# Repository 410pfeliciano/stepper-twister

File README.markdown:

=================================
An open-source, very fast tetrode twister for Arduino
=================================

This code requires the [Arduino](http://www.arduino.cc) development environment and an [Arduino board](http://www.sparkfun.com/products/11021>). 

The code has been updated to be compatible with the Arduino IDE version 1.0 and higher. To make it compatible with earlier versions of the IDE, simply include "WProgram.h" instead of "Arduino.h" in the TwisterClasses.h file.

This repository contains circuit board files, a parts list, and an instruction manual.

=================================
Attribution
=================================
This work is basically a direct combination of two existing open-source projects:

1. "Tetrode Twister" by Josh Siegle, which is licensed under [GPLv3](http://www.gnu.org/licenses/gpl-3.0.txt)
    * [Josh on Github](https://github.com/jsiegle)
    * [Twister Project](https://github.com/open-ephys/twister)

2. "Easy Driver" by Brian Schmalz, which is  is licensed under [CC-BY-3.0](https://creativecommons.org/licenses/by/3.0/us/)
    * [Brian's site](http://www.schmalzhaus.com/)
    * [Easy Driver Project](http://www.schmalzhaus.com/EasyDriver/)

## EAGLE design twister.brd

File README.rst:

=================================
An open-source, very fast tetrode twister for Arduino
=================================

This code requires the [Arduino](http://www.arduino.cc) development environment and an [Arduino board](http://www.sparkfun.com/products/11021>). 

The code has been updated to be compatible with the Arduino IDE version 1.0 and higher. To make it compatible with earlier versions of the IDE, simply include "WProgram.h" instead of "Arduino.h" in the TwisterClasses.h file.

This repository contains circuit board files, a parts list, and an instruction manual.

=================================
Attribution
=================================
This work is basically a direct combination of two existing open-source projects:

1. "Tetrode Twister" by Josh Siegle, which is licensed under [GPLv3](http://www.gnu.org/licenses/gpl-3.0.txt)
--* [Josh on Github](https://github.com/jsiegle)
--* [Twister Project](https://github.com/open-ephys/twister)

2. "Easy Driver" by Brian Schmalz, which is  is licensed under [CC-BY-3.0](https://creativecommons.org/licenses/by/3.0/us/)
--* [Brian's site](http://www.schmalzhaus.com/)
--* [Easy Driver Project](http://www.schmalzhaus.com/EasyDriver/)

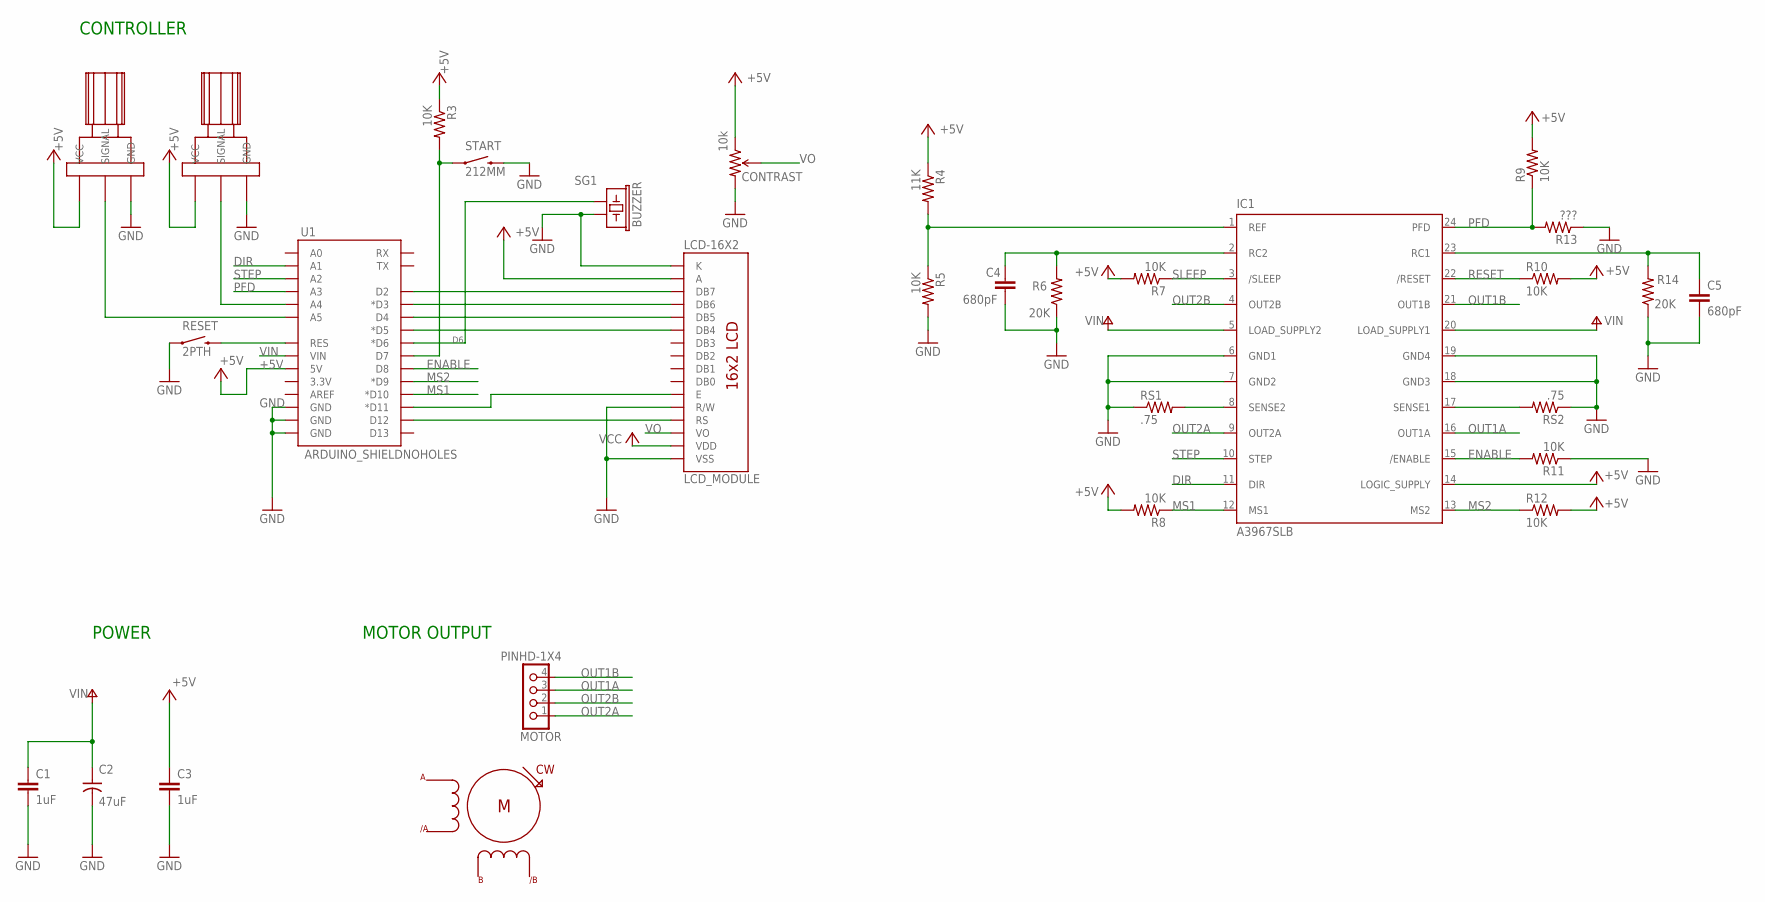
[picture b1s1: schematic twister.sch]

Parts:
BUZZER: SG1; BUZZER-12MM
C1, C3: 1uF; 0805
C2: 47uF; 153CLV-0807
C4, C5: 680pF; 0603
CONTRAST: 10k; 3362U-2
IC1: A3967SLB; SO24W
LCD_MODULE: LCD-16X2
MOTOR: PINHD-1X4; 1X04
R1, R2: R12-0; LARGE_POT
R3, R5, R7, R8, R9, R10, R11, R12: 10K; 0603
R4: 11K; 0603
R6, R14: 20K; 0603
R13: ???; 0603
RESET: 2PTH; TACTILE-PTH
RS1, RS2: .75; 1206
START: 212MM; TACTILE-PTH-12MM
STEPPER: ST-PM35; ST-PM35-15-11C
U1: ARDUINO_SHIELDNOHOLES; DUEMILANOVE_SHIELD_NOHOLES

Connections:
D6: BUZZER.- (2), U1.D6 (*D6)
DIR: IC1.11 (DIR), U1.A1
ENABLE: IC1.15 (/ENABLE), R11.2, U1.D8
GND: BUZZER.+ (1), C1.2, C2.-, C3.2, C4.2, C5.2, CONTRAST.3 (CW), IC1.6 (GND1), IC1.7 (GND2), IC1.18 (GND3), IC1.19 (GND4), LCD_MODULE.1 (VSS), LCD_MODULE.5 (R/W), LCD_MODULE.16 (K), R1.RIGHT (GND), R2.RIGHT (GND), R5.2, R6.1, R11.1, R13.1, R14.1, RESET.1, RS1.1, RS2.1, START.3 (2), U1.GND@0 (GND), U1.GND@1 (GND), U1.GND@2 (GND)
MS1: IC1.12 (MS1), R8.1, U1.D10 (*D10)
MS2: IC1.13 (MS2), R12.1, U1.D9 (*D9)
unnamed: IC1.8 (SENSE2), RS1.2
unnamed: C4.1, IC1.2 (RC2), R6.2
unnamed: IC1.17 (SENSE1), RS2.2
unnamed: LCD_MODULE.4 (RS), U1.D12
unnamed: LCD_MODULE.6 (E), U1.D11 (*D11)
unnamed: LCD_MODULE.11 (DB4), U1.D5 (*D5)
unnamed: LCD_MODULE.12 (DB5), U1.D4
unnamed: LCD_MODULE.13 (DB6), U1.D3 (*D3)
unnamed: LCD_MODULE.14 (DB7), U1.D2
unnamed: R2.CENTER (SIGNAL), U1.A4
unnamed: R1.CENTER (SIGNAL), U1.A5
unnamed: R3.2, START.1, U1.D7
unnamed: C5.1, IC1.23 (RC1), R14.2
unnamed: IC1.1 (REF), R4.2, R5.1
OUT1A: IC1.16 (OUT1A), MOTOR.3
OUT1B: IC1.21 (OUT1B), MOTOR.4
OUT2A: IC1.9 (OUT2A), MOTOR.1
OUT2B: IC1.4 (OUT2B), MOTOR.2
PFD: IC1.24 (PFD), R9.1, R13.2, U1.A3
RESET: IC1.22 (/RESET), R10.1, RESET.3 (2), U1.RES
SLEEP: IC1.3 (/SLEEP), R7.1
STEP: IC1.10 (STEP), U1.A2
VIN: C1.1, C2.+, IC1.5 (LOAD_SUPPLY2), IC1.20 (LOAD_SUPPLY1), U1.VIN
VO: CONTRAST.2 (WIPER), LCD_MODULE.3 (VO)

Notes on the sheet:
POWER
CONTROLLER
MOTOR OUTPUT

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
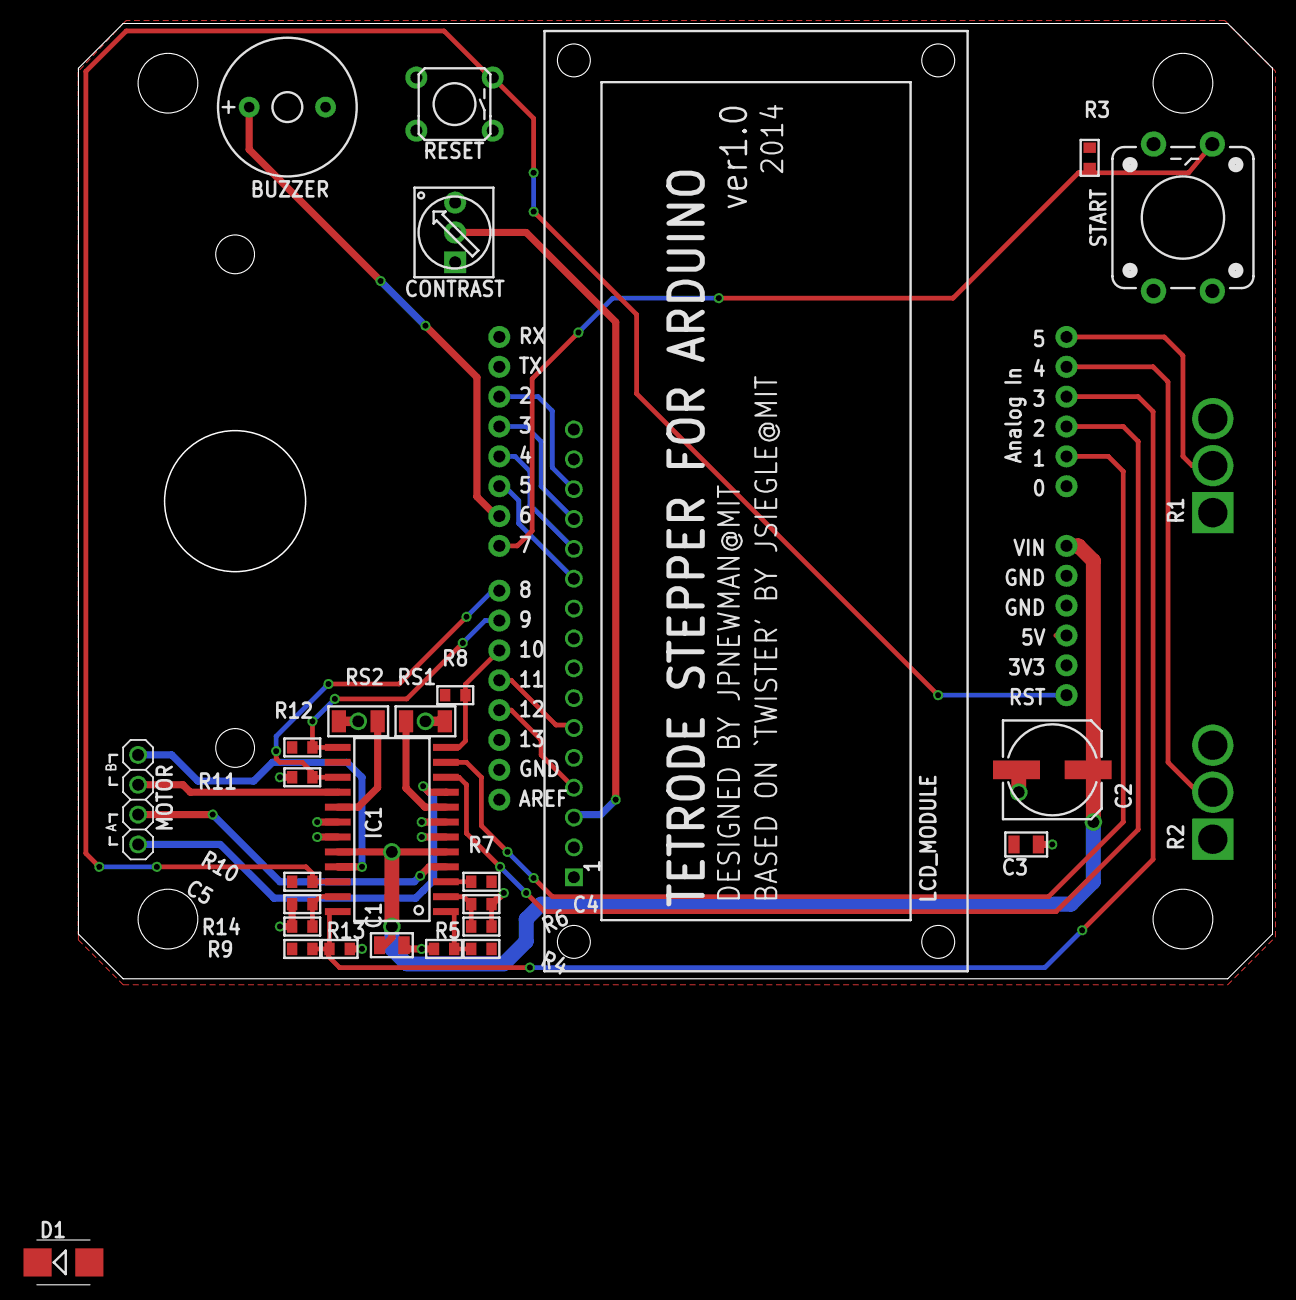
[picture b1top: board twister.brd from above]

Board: 2 copper layers, 101.6 x 81.3 mm, 31 parts (1 on the bottom side), 32 nets.

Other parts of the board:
D1: DIODE_SMB; SMB

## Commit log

2014-09-23 Added the easy driver board an simply imported into the existing twister design.
2014-09-23 Renamed README.
2014-09-23 Fixed markdown syntax.
2014-09-25 Got rid of unnessary jumpers on stepper driver circuit and instead sent to open io pins on arduino.
2014-09-25 Added stepper motor.
2014-09-27 Everything should be set for final layout.
2014-09-28 Halfway through layout.
2014-09-29 Just about finished. Need to clean up aux materials so they actually match the pcb.
2014-10-01 Finished rev 1.0 and sent to fab.
2014-10-16 Put together first PCB, started documenting improvements.
2014-10-16 cam and bom updates.
2014-10-16 Semi functional code.
2014-10-17 System is working pretty well. I need a better way to couple the motor shaft to the arm piece.
2014-10-31 Designed a new tetrode holder capable of handling the high speeds of the twister.
2014-10-31 Finished the new tetrode holder. Ordered parts.
2014-10-31 Update BOM.
